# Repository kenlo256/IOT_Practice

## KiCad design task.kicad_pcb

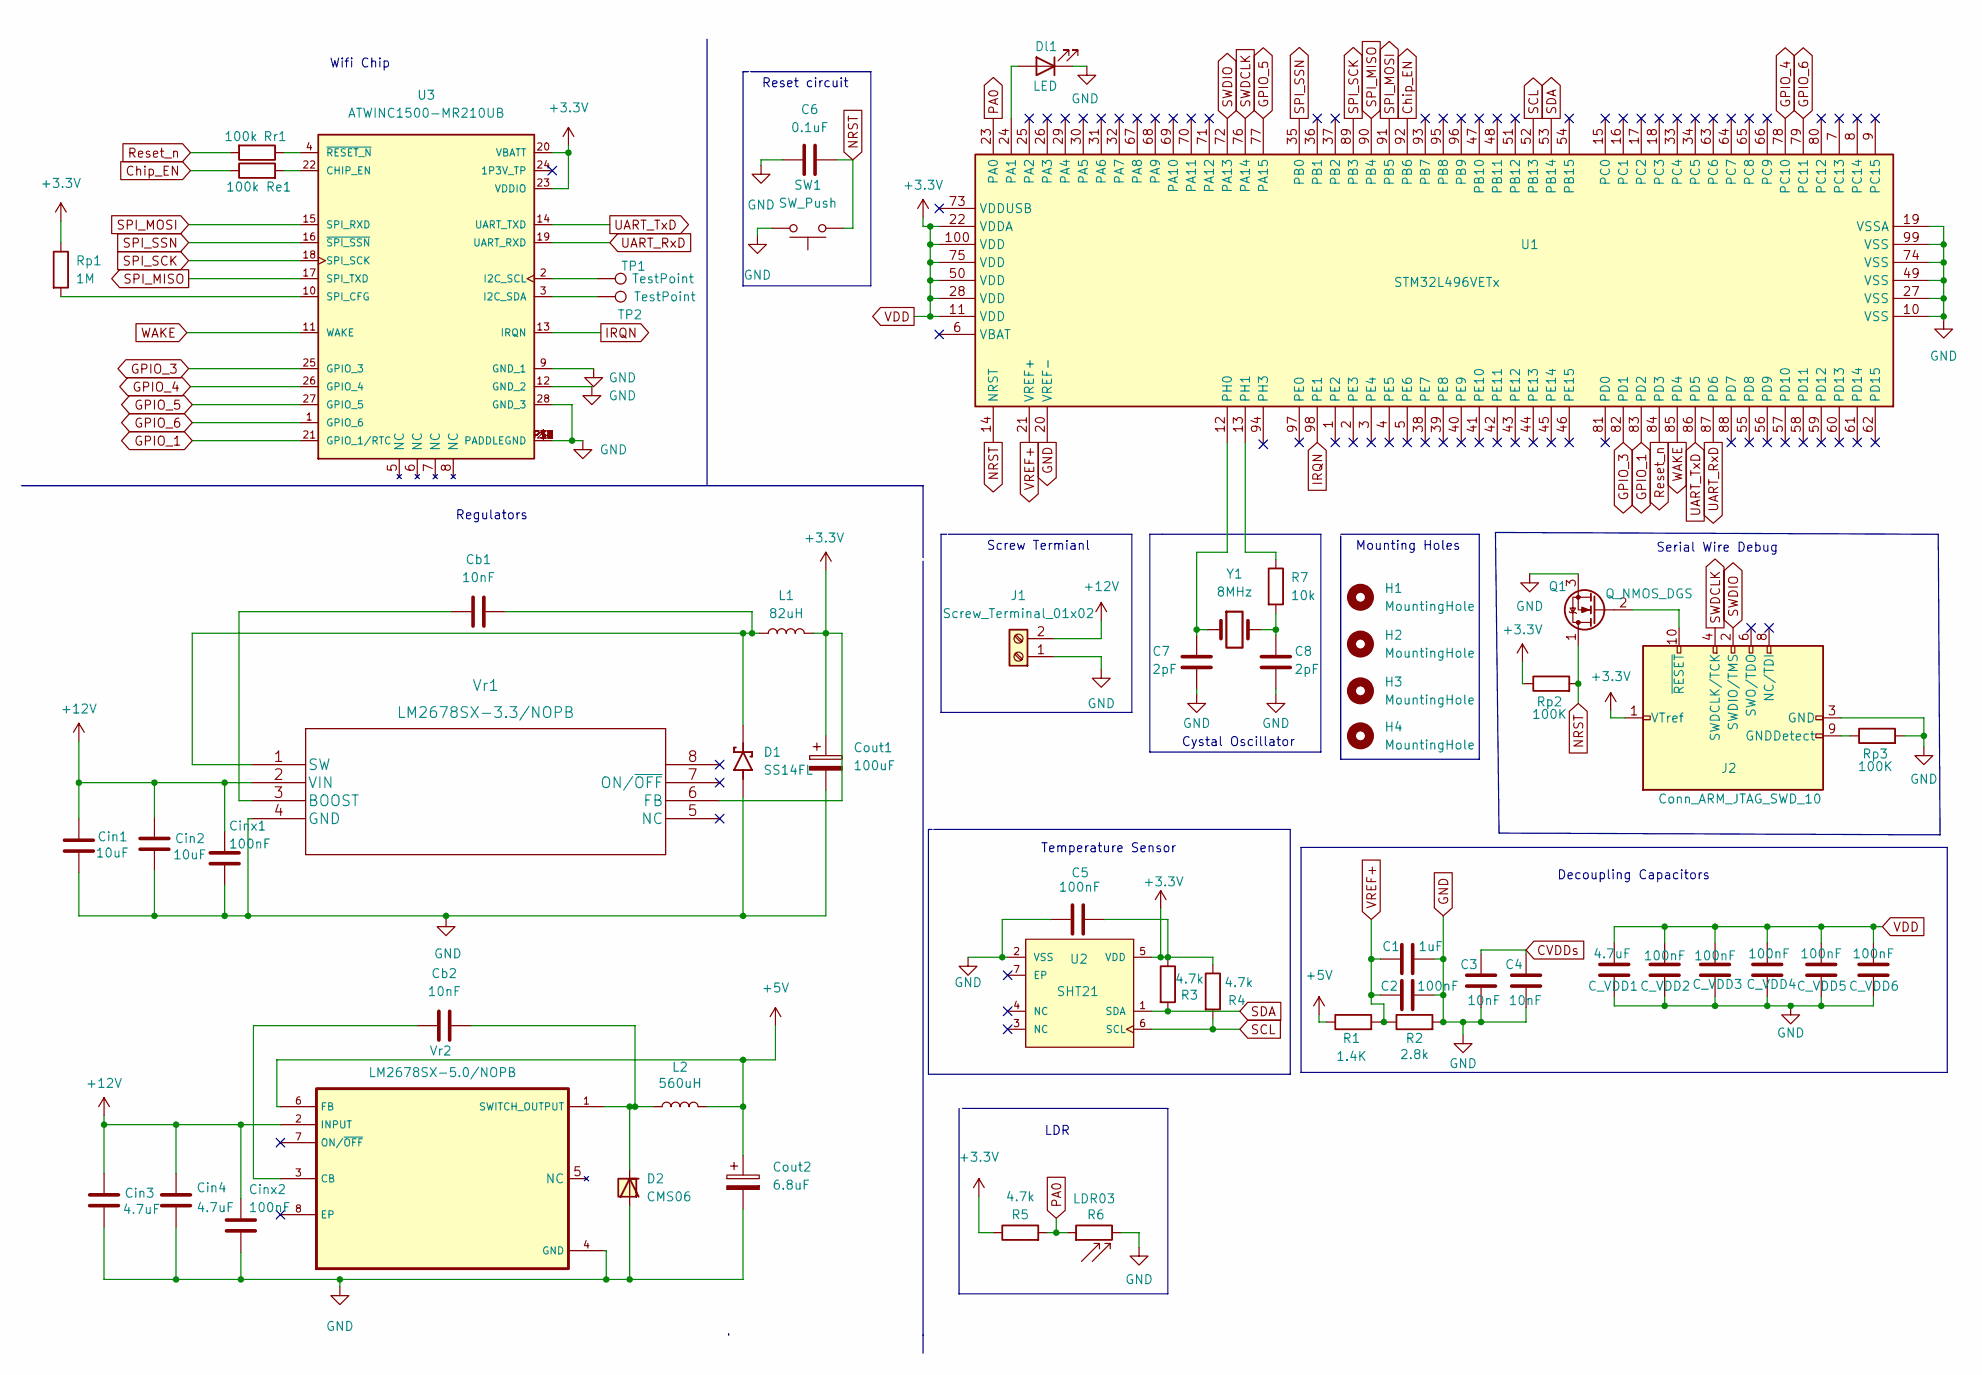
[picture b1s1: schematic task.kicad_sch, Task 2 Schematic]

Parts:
C1: 1uF; C_1206_3216Metric
C2: 100nF; C_0402_1005Metric
C3, C4: 10nF; C_0201_0603Metric
C5: 100nF; C_0805_2012Metric
C6: 0.1uF; C_1206_3216Metric
C7, C8: 2pF; C_0402_1005Metric
C_VDD1: 4.7uF; C_1206_3216Metric
C_VDD2, C_VDD3, C_VDD4, C_VDD5, C_VDD6: 100nF; C_0805_2012Metric
Cb1, Cb2: 10nF; C_0805_2012Metric
Cin1, Cin2: 10uF; C_1206_3216Metric
Cin3, Cin4: 4.7uF; C_1206_3216Metric
Cinx1, Cinx2: 100nF; C_0402_1005Metric
Cout1: 100uF; CP_EIA-6032-28_Kemet-C
Cout2: 6.8uF; CP_EIA-3216-18_Kemet-A
D1: SS14FL; SODFL3617X108N; PARTREV 2
D2: CMS06; SMADIODE
Dl1: LED; LED_0402_1005Metric
H1, H2, H3, H4: MountingHole; MountingHole_2.2mm_M2
J1: Screw_Terminal_01x02; PhoenixContact_MSTBA_2,5_2-G-5,08_1x02_P5.08mm_Horizontal
J2: Conn_ARM_JTAG_SWD_10; PinHeader_2x05_P1.27mm_Vertical
L1: 82uH; L_TDK_SLF6028
L2: 560uH; L_Bourns_SRR1260
Q1: Q_NMOS_DGS; SOT-23
R1: 1.4K; R_0603_1608Metric
R2: 2.8k; R_0603_1608Metric
R3, R4, R5: 4.7k; R_0603_1608Metric
R6: LDR03; R_LDR_10x8.5mm_P7.6mm_Vertical
R7: 10k; R_1206_3216Metric
Re1: 100k; R_1206_3216Metric
Rp1: 1M; R_0603_1608Metric
Rp2, Rp3: 100K; R_1206_3216Metric
Rr1: 100k; R_1206_3216Metric
SW1: SW_Push; SW_Push_1P1T_NO_CK_KMR2
TP1, TP2: TestPoint; TestPoint_Pad_D1.0mm
U1: STM32L496VETx; LQFP-100_14x14mm_P0.5mm
U2: SHT21; Sensirion-SHT21-Manufacturer_Recommended; Frequency Tolerance 30ppm; Tolerance 30ppm
U3: ATWINC1500-MR210UB; MICROCHIP_ATWINC1500-MR210UB
Vr1: LM2678SX-3.3/NOPB; LM2678SX-3.3&slash_NOPB
Vr2: LM2678SX-5.0/NOPB; TO127P1435X464-8N
Y1: 8MHz; Crystal_SMD_TXC_9HT11-2Pin_2.0x1.2mm

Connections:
+5V: Cout2.1, L2.2, R1.1, Vr2.6 (FB)
+12V: Cin1.1, Cin2.1, Cin3.1, Cin4.1, Cinx1.1, Cinx2.1, J1.2, Vr1.2 (VIN), Vr2.2 (INPUT)
CVDDs: C3.2, C4.2
Chip_EN: Re1.1, U1.92 (PB6)
GND: C1.2, C2.2, C3.1, C4.1, C5.2, C6.1, C7.2, C8.2, C_VDD1.2, C_VDD2.2, C_VDD3.2, C_VDD4.2, C_VDD5.2, C_VDD6.2, Cin1.2, Cin2.2, Cin3.2, Cin4.2, Cinx1.2, Cinx2.2, Cout1.2, Cout2.2, D1.A, D2.A, Dl1.1 (K), J1.1, J2.3 (GND), J2.5 (GND), Q1.3 (S), R2.2, R6.2, Rp3.2, SW1.2, U1.10 (VSS), U1.19 (VSSA), U1.20 (VREF-), U1.27 (VSS), U1.49 (VSS), U1.74 (VSS), U1.99 (VSS), U2.2 (VSS), U3.9 (GND_1), U3.12 (GND_2), U3.28 (GND_3), U3.29 (PADDLEGND), U3.P$1 (PADDLEGND), U3.P$2 (PADDLEGND), U3.P$3 (PADDLEGND), U3.P$4 (PADDLEGND), U3.P$5 (PADDLEGND), U3.P$6 (PADDLEGND), U3.P$7 (PADDLEGND), U3.P$8 (PADDLEGND), U3.P$9 (PADDLEGND), Vr1.4 (GND), Vr2.4 (GND)
GPIO_1: U1.83 (PD2), U3.21 (GPIO_1/RTC)
GPIO_3: U1.82 (PD1), U3.25 (GPIO_3)
GPIO_4: U1.78 (PC10), U3.26 (GPIO_4)
GPIO_5: U1.77 (PA15), U3.27 (GPIO_5)
GPIO_6: U1.79 (PC11), U3.1 (GPIO_6)
IRQN: U1.98 (PE1), U3.13 (IRQN)
NRST: C6.2, Q1.1 (D), Rp2.2, SW1.1, U1.14 (NRST)
unnamed: C8.1, R7.2, Y1.2
unnamed: Cb1.1, Vr1.3 (BOOST)
unnamed: Cb1.2, D1.C, L1.1, Vr1.1 (SW)
unnamed: Cb2.1, Vr2.3 (CB)
unnamed: Cb2.2, D2.C, L2.1, Vr2.1 (SWITCH_OUTPUT)
unnamed: Dl1.2 (A), U1.24 (PA1)
unnamed: J2.9 (GNDDetect), Rp3.1
unnamed: J2.10 (~RESET), Q1.2 (G)
unnamed: Re1.2, U3.22 (CHIP_EN)
unnamed: Rp1.2, U3.10 (SPI_CFG)
unnamed: Rr1.1, U3.4 (~RESET_N)
unnamed: TP1.1, U3.2 (I2C_SCL)
unnamed: TP2.1, U3.3 (I2C_SDA)
unnamed: C7.1, U1.12 (PH0), Y1.1
unnamed: R7.1, U1.13 (PH1)
PA0: R5.2, R6.1, U1.23 (PA0)
Reset_n: Rr1.2, U1.84 (PD3)
SCL: R4.2, U1.52 (PB13), U2.6 (SCL)
SDA: R3.2, U1.53 (PB14), U2.1 (SDA)
SPI_MISO: U1.90 (PB4), U3.17 (SPI_TXD)
SPI_MOSI: U1.91 (PB5), U3.15 (SPI_RXD)
SPI_SCK: U1.89 (PB3), U3.18 (SPI_SCK)
SPI_SSN: U1.35 (PB0), U3.16 (~SPI_SSN)
SWDCLK: J2.4 (SWDCLK/TCK), U1.76 (PA14)
SWDIO: J2.2 (SWDIO/TMS), U1.72 (PA13)
UART_RxD: U1.87 (PD6), U3.19 (UART_RXD)
UART_TxD: U1.86 (PD5), U3.14 (UART_TXD)
VDD: C5.1, C_VDD1.1, C_VDD2.1, C_VDD3.1, C_VDD4.1, C_VDD5.1, C_VDD6.1, Cout1.1, J2.1 (VTref), L1.2, R3.1, R4.1, R5.1, Rp1.1, Rp2.1, U1.11 (VDD), U1.22 (VDDA), U1.28 (VDD), U1.50 (VDD), U1.75 (VDD), U1.100 (VDD), U2.5 (VDD), U3.20 (VBATT), U3.23 (VDDIO), Vr1.6 (FB)
VREF+: C1.1, C2.1, R1.2, R2.1, U1.21 (VREF+)
WAKE: U1.85 (PD4), U3.11 (WAKE)

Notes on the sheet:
Cystal Oscillator
Decoupling Capacitors
Regulators
Temperature Sensor
Screw Termianl
Serial Wire Debug
Wifi Chip
LDR
Reset circuit
Mounting Holes

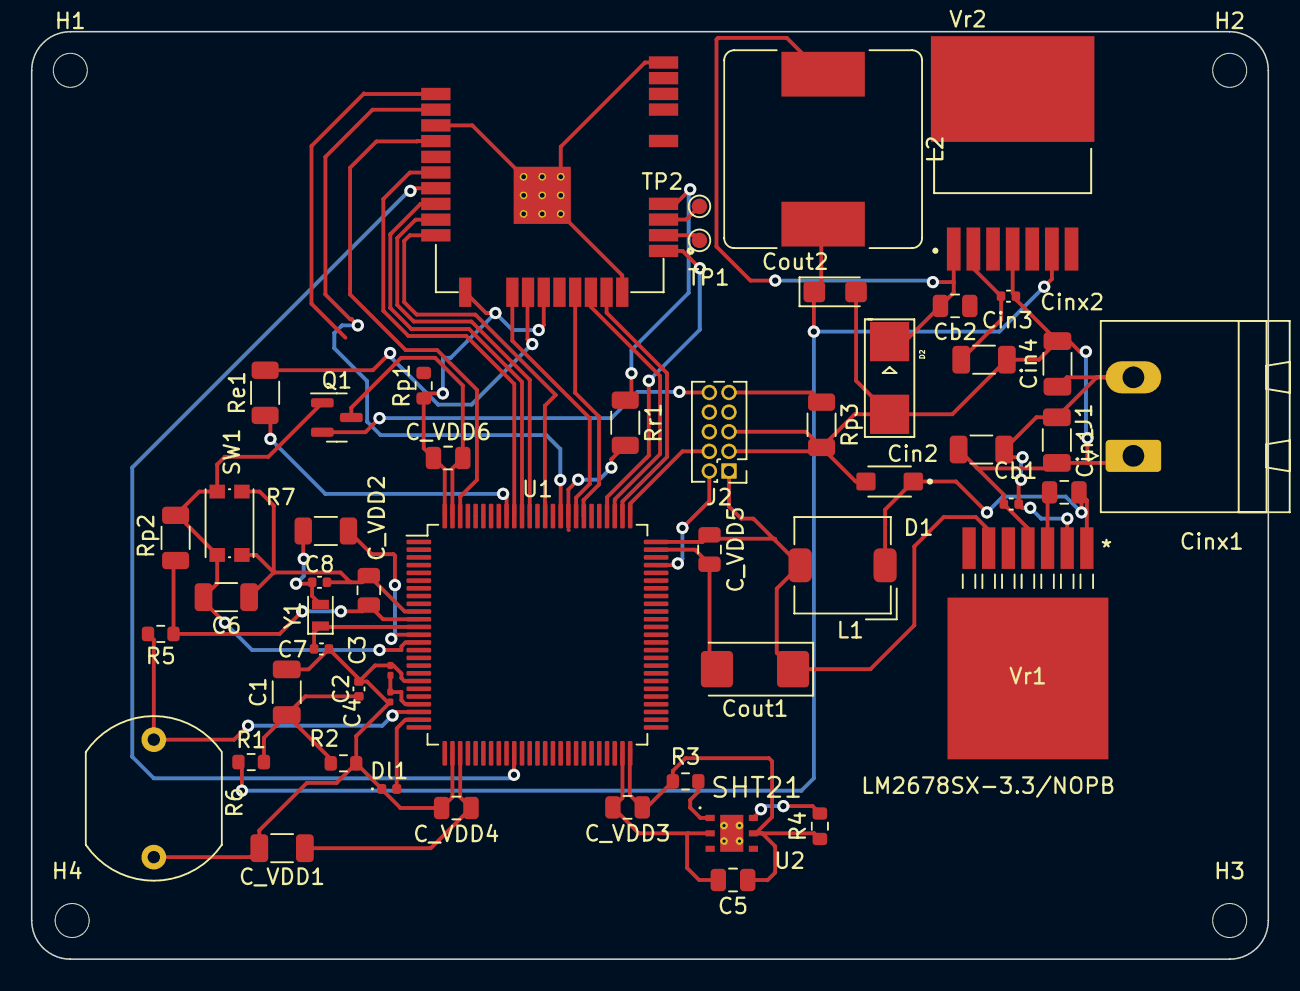
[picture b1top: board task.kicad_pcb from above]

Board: 4 copper layers, 80.0 x 60.0 mm, 57 parts (0 on the bottom side), 42 nets.

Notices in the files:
parts and their libraries:
Copyright 2021 Accelerated Designs. All rights reserved.
